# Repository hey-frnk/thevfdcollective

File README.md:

# Fluorescence by The VFD Collective

Glad to see you, welcome to the repository of Fluorescence by The VFD Collective. While having a colorful time, here are a few places to roam freely:
  - FluorescenceV3: (active) Source code of firmware version 3.0 for OpenVFD & Fluorescence. Includes source code for Arduino, STM32 HAL and simulation with Qt GUI
  - FluorescenceApp: (active) Source code of the app for OpenVFD & Fluorescence. The cross platform app enables communicating to Fluorescence over USB and Bluetooth
  
  - FluorescenceCompiled: (active) Official compiled versions of FluorescenceApp and firmware files for Fluorescence
  - hardware: (active) Public Fluorescence/OpenVFD Eagle files. Includes libraries and published PCB designs

No longer updated, kept for reference only:
  - openvfd_firmware: (V2 Legacy) Those sparking code lines for OpenVFD & Fluorescence. The cool thing about the firmware is that it is only one single file. Throw it into your Arduino IDE, compile and have fun. Oh and don't forget to tear it apart and get creative yourself
  - myOpenVFD-vs: (V2 Legacy) Source code of myOpenVFD Windows application

Cheers.</br>
Frank from The VFD Collective

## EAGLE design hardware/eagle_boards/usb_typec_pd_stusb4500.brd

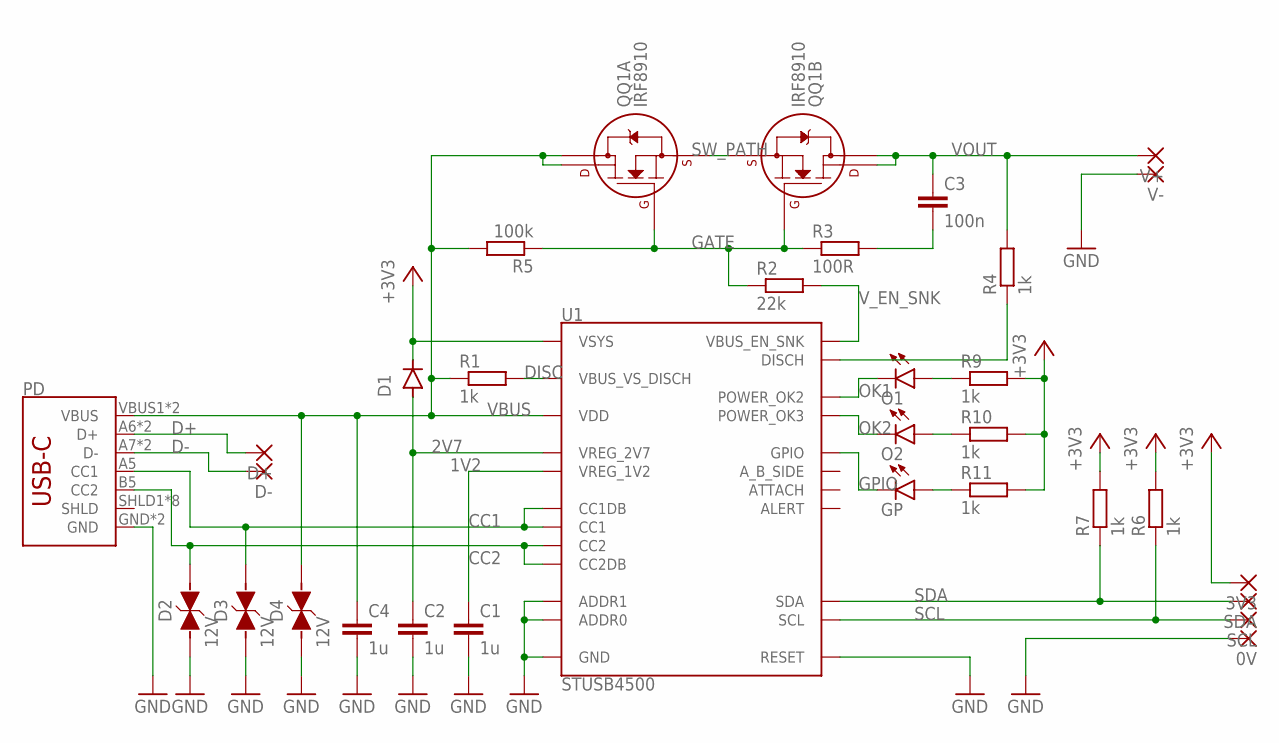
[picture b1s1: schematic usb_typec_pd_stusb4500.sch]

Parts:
0V, 3V3: SMD2; SMD1,27-2,54
C1, C2, C4: 1u; C0805
C3: 100n; C0805
D1: DIODE-SOD123; SOD123
D2, D3, D4: 12V; WE-VE_0805
D+: SMD2; SMD1,27-2,54
D-: SMD2; SMD1,27-2,54
GP: LEDCHIP-LED0805; CHIP-LED0805
O1, O2: LEDCHIP-LED0805; CHIP-LED0805
PD: USB-TYPEC-16PIN2-LAYER; USB-C-16P
QQ1: IRF8910; SO-8
R1, R4, R6, R7, R9, R10, R11: 1k; R0805
R2: 22k; R0805
R3: 100R; R0805
R5: 100k; R0805
SCL: SMD2; SMD1,27-2,54
SDA: SMD2; SMD1,27-2,54
U1: STUSB4500; POWER-QFN-24
V+: SMD2; SMD1,27-2,54
V-: SMD2; SMD1,27-2,54

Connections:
1V2: C1.1, U1.P$21 (VREG_1V2)
2V7: C2.1, D1.A, U1.P$23 (VREG_2V7)
+3V3: 3V3.1, D1.C, R6.2, R7.2, R9.2, R10.2, R11.2, U1.P$22 (VSYS)
CC1: D3.1, PD.A5 (CC1), U1.P$1 (CC1DB), U1.P$2 (CC1)
CC2: D2.1, PD.B5 (CC2), U1.P$4 (CC2), U1.P$5 (CC2DB)
D+: D+.1, PD.A6 (D+), PD.B6 (D+)
D-: D-.1, PD.A7 (D-), PD.B7 (D-)
DISC: R1.2, U1.P$18 (VBUS_VS_DISCH)
GATE: QQ1.2 (G), QQ1.4 (G), R2.1, R3.1, R5.1
GND: 0V.1, C1.2, C2.2, C4.2, D2.2, D3.2, D4.2, PD.GND, PD.GND2 (GND), U1.P$6 (RESET), U1.P$10 (GND), U1.P$12 (ADDR0), U1.P$13 (ADDR1), U1.P$25 (GND), V-.1
GPIO: GP.C, U1.P$15 (GPIO)
unnamed: C3.2, R3.2
unnamed: R4.1, U1.P$9 (DISCH)
unnamed: O1.A, R9.1
unnamed: O2.A, R10.1
unnamed: GP.A, R11.1
OK1: O1.C, U1.P$20 (POWER_OK2)
OK2: O2.C, U1.P$14 (POWER_OK3)
SCL: R6.1, SCL.1, U1.P$7 (SCL)
SDA: R7.1, SDA.1, U1.P$8 (SDA)
SW_PATH: QQ1.1 (S), QQ1.3 (S)
VBUS: C4.1, D4.1, PD.VBUS1 (VBUS), PD.VBUS2 (VBUS), QQ1.7 (D2), QQ1.8 (D1), R1.1, R5.2, U1.P$24 (VDD)
VOUT: C3.1, QQ1.5 (D2), QQ1.6 (D1), R4.2, V+.1
V_EN_SNK: R2.2, U1.P$16 (VBUS_EN_SNK)

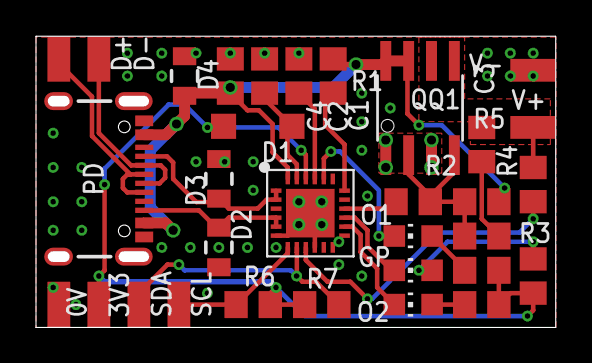
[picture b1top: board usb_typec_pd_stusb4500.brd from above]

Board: 2 copper layers, 28.9 x 16.2 mm, 32 parts (0 on the bottom side), 24 nets.

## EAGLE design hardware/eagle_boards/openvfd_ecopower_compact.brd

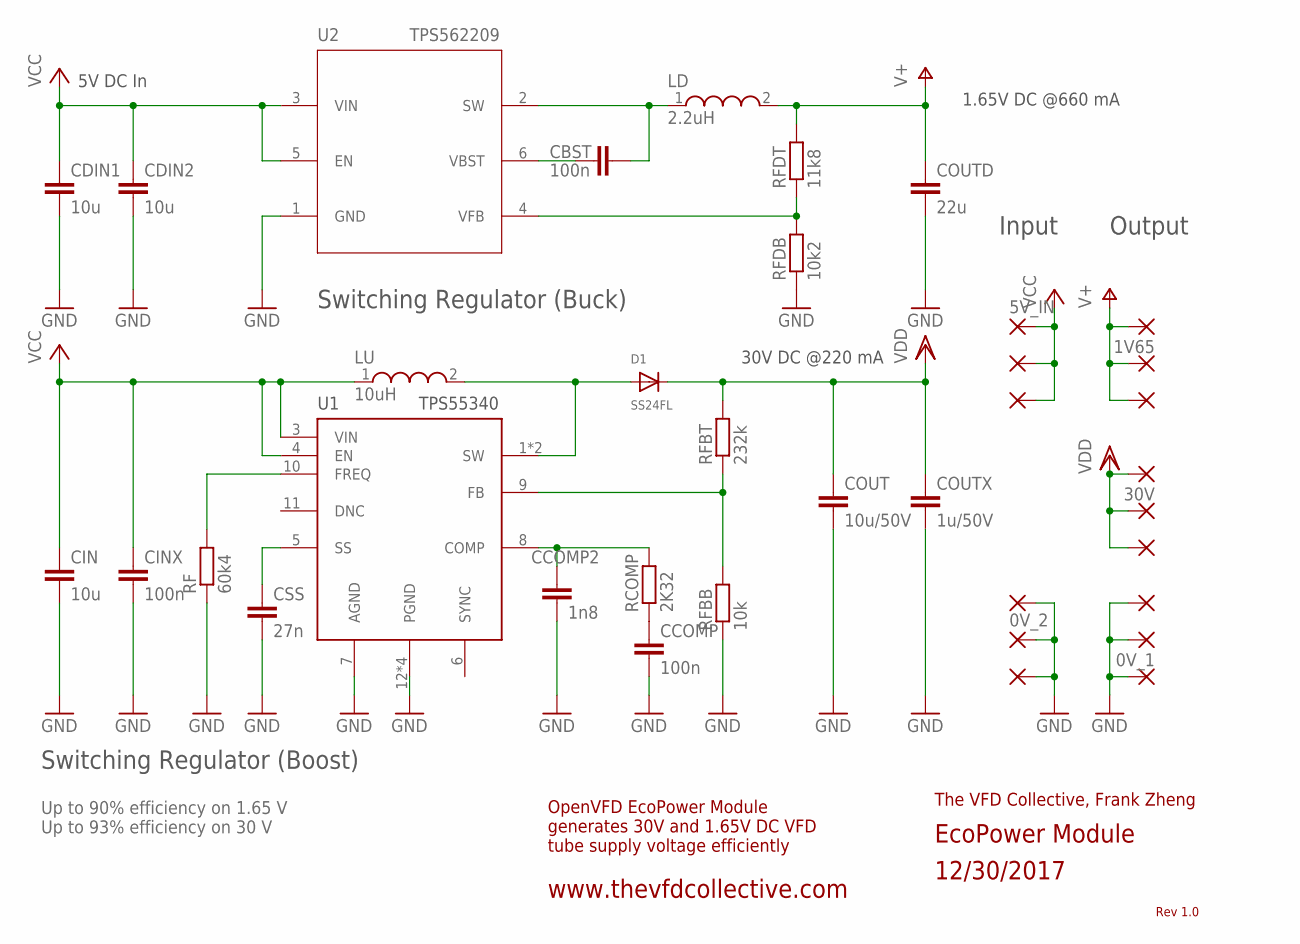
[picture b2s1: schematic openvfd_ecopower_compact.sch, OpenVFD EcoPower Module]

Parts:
0V_1, 0V_2, 0V_3, 0V_4, 1V1, 1V65, 5V_IN, 5V_IN1, 30V, 30V1: SMD2; SMD1,27-2,54
CBST: 100n; C0805
CCOMP: 100n; C0805
CCOMP2: 1n8; C0805
CDIN1, CDIN2: 10u; C0805
CIN: 10u; C0805
CINX: 100n; C0805
COUT: 10u/50V; C1206
COUTD: 22u; C0805
COUTX: 1u/50V; C0805
CSS: 27n; C0805
D1: SS24FL; SOD-123FL
LD: 2.2uH; WE-TPC_4818/4828
LU: 10uH; WE-LQS_6045
PAD1, PAD2, PAD3, PAD4, PAD5: 1,6/0,8
RCOMP: 2K32; R0805
RF: 60k4; R0805
RFBB: 10k; R0805
RFBT: 232k; R0805
RFDB: 10k2; R0805
RFDT: 11k8; R0805
U1: TPS55340; HTSSOP-14
U2: TPS562209; SOT-23(6)

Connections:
COMP: CCOMP2.1, RCOMP.2, U1.8 (COMP)
FB: RFBB.2, RFBT.1, U1.9 (FB)
FREQ: RF.2, U1.10 (FREQ)
GND: 0V_1.1, 0V_2.1, 0V_3.1, 0V_4.1, CCOMP.2, CCOMP2.2, CDIN1.2, CDIN2.2, CIN.2, CINX.2, COUT.2, COUTD.2, COUTX.2, CSS.2, PAD1.1, PAD5.1, RF.1, RFBB.1, RFDB.1, U1.7 (AGND), U1.12 (PGND), U1.13 (PGND), U1.14 (PGND), U1.15 (PGND), U2.1 (GND)
unnamed: CCOMP.1, RCOMP.1
unnamed: CBST.1, U2.6 (VBST)
unnamed: RFDB.2, RFDT.1, U2.4 (VFB)
SS: CSS.1, U1.5 (SS)
SW: D1.A, LU.2, U1.1 (SW), U1.2 (SW)
V+: 1V1.1, 1V65.1, COUTD.1, LD.2, PAD3.1, RFDT.2
VCC: 5V_IN.1, 5V_IN1.1, CDIN1.1, CDIN2.1, CIN.1, CINX.1, LU.1, PAD2.1, U1.3 (VIN), U1.4 (EN), U2.3 (VIN), U2.5 (EN)
VDD: 30V.1, 30V1.1, COUT.1, COUTX.1, D1.C, PAD4.1, RFBT.2
VSW_D: CBST.2, LD.1, U2.2 (SW)

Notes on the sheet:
Input
Output
30V DC @220 mA
1.65V DC @660 mA
EcoPower Module
12/30/2017
5V DC In
Up to 90% efficiency on 1.65 V Up to 93% efficiency on 30 V
Rev 1.0
OpenVFD EcoPower Module generates 30V and 1.65V DC VFD tube supply voltage efficiently
www.thevfdcollective.com
The VFD Collective, Frank Zheng
Switching Regulator (Buck)
Switching Regulator (Boost)

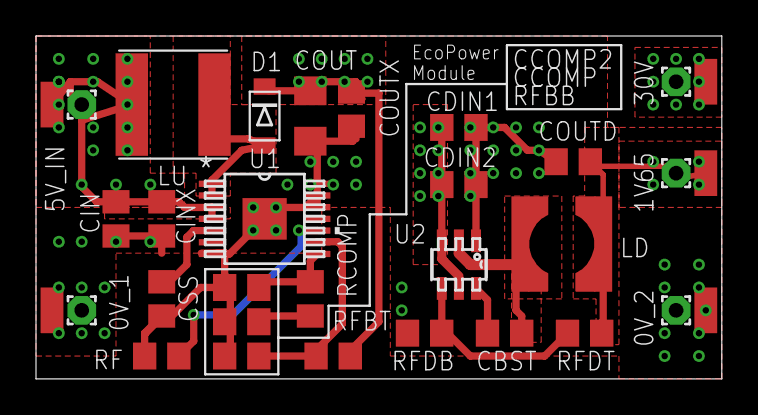
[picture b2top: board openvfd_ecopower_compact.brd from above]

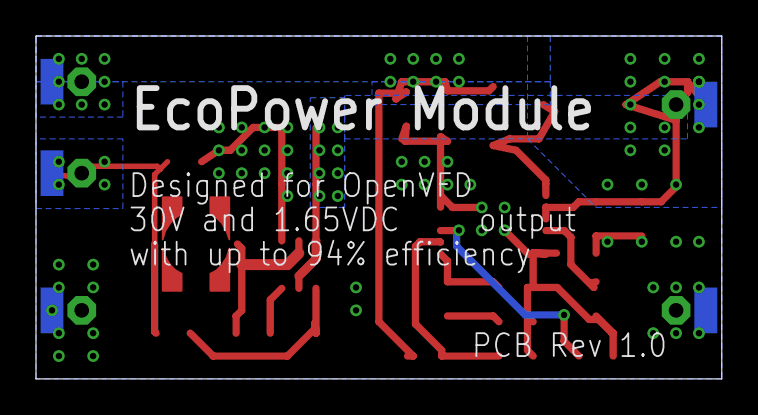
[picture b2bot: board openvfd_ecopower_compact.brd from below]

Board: 2 copper layers, 38.1 x 19.1 mm, 37 parts (5 on the bottom side), 13 nets.

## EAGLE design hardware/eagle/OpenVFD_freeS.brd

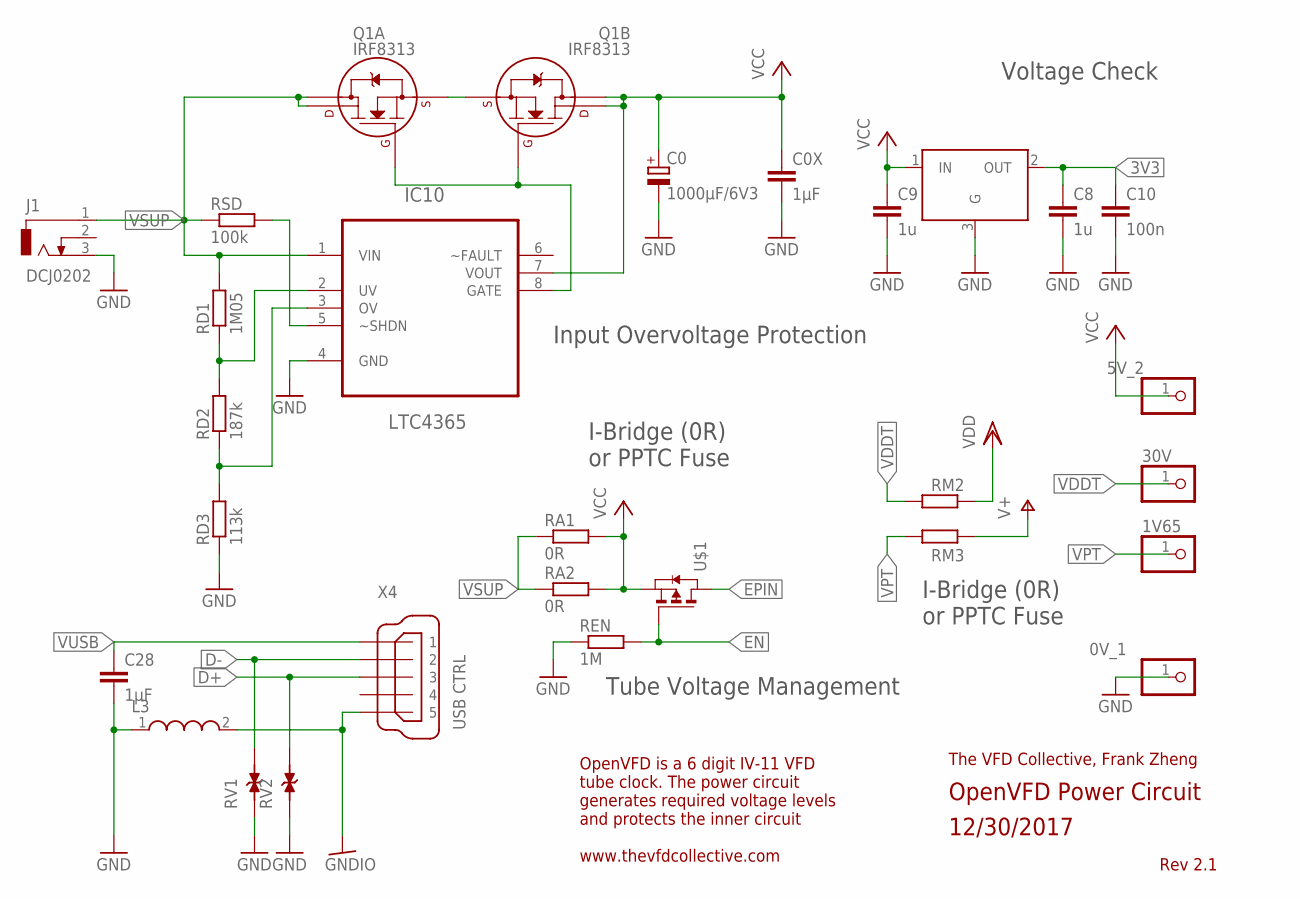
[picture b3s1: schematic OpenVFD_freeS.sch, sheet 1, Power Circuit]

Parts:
0V_1, 1V65, 5V_2, 30V: PINHD-1X1; 1X01
C0: 1000µF/6V3; 153CLV-1010
C0X, C28: 1µF; C0805
C8, C9: 1u; C0805
C10: 100n; C0805
IC9: AP7313; SOT23-R
IC10: LTC4365; SOT65P280X100-8N
J1: DCJ0202
L3: WE-CBF_0805(HC); WE-CBF_0805(W=4.0)
Q1: IRF8313; SO-8
RA1, RA2: 0R; R1210
RD1: 1M05; R0805
RD2: 187k; R0805
RD3: 113k; R0805
REN: 1M; R0805
RM2, RM3: 0R; R1210
RSD: 100k; R0805
RV1, RV2: WE-VE_0805_82350120101; WESURGE_0805_REFLOW
U$1: PMOSSOT223; SOT223
X4: USB CTRL; 32005-201

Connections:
3V3: C8.1, C10.1, IC9.2 (OUT); also elsewhere on the board
D+: RV2.1, X4.3; also elsewhere on the board
D-: RV1.1, X4.2; also elsewhere on the board
GATE: IC10.8 (GATE), Q1.2 (G), Q1.4 (G)
GNDIO: L3.2, X4.5; also elsewhere on the board
unnamed: REN.2, U$1.1 (G)
OV: IC10.3 (OV), RD2.1, RD3.2
SHDN: IC10.5 (~SHDN), RSD.2
SOURCE: Q1.1 (S), Q1.3 (S)
UV: IC10.2 (UV), RD1.1, RD2.2
V+: RM3.2; also elsewhere on the board
VDD: RM2.2; also elsewhere on the board
VDDT: 30V.1, RM2.1; also elsewhere on the board
VPT: 1V65.1, RM3.1; also elsewhere on the board
VSUP: IC10.1 (VIN), J1.1, Q1.7 (D2), Q1.8 (D1), RA1.1, RA2.1, RD1.2, RSD.1

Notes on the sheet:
Input Overvoltage Protection
I-Bridge (0R) or PPTC Fuse
Tube Voltage Management
Voltage Check
The VFD Collective, Frank Zheng
OpenVFD Power Circuit
12/30/2017
Rev 2.1
OpenVFD is a 6 digit IV-11 VFD tube clock. The power circuit generates required voltage levels and protects the inner circuit www.thevfdcollective.com

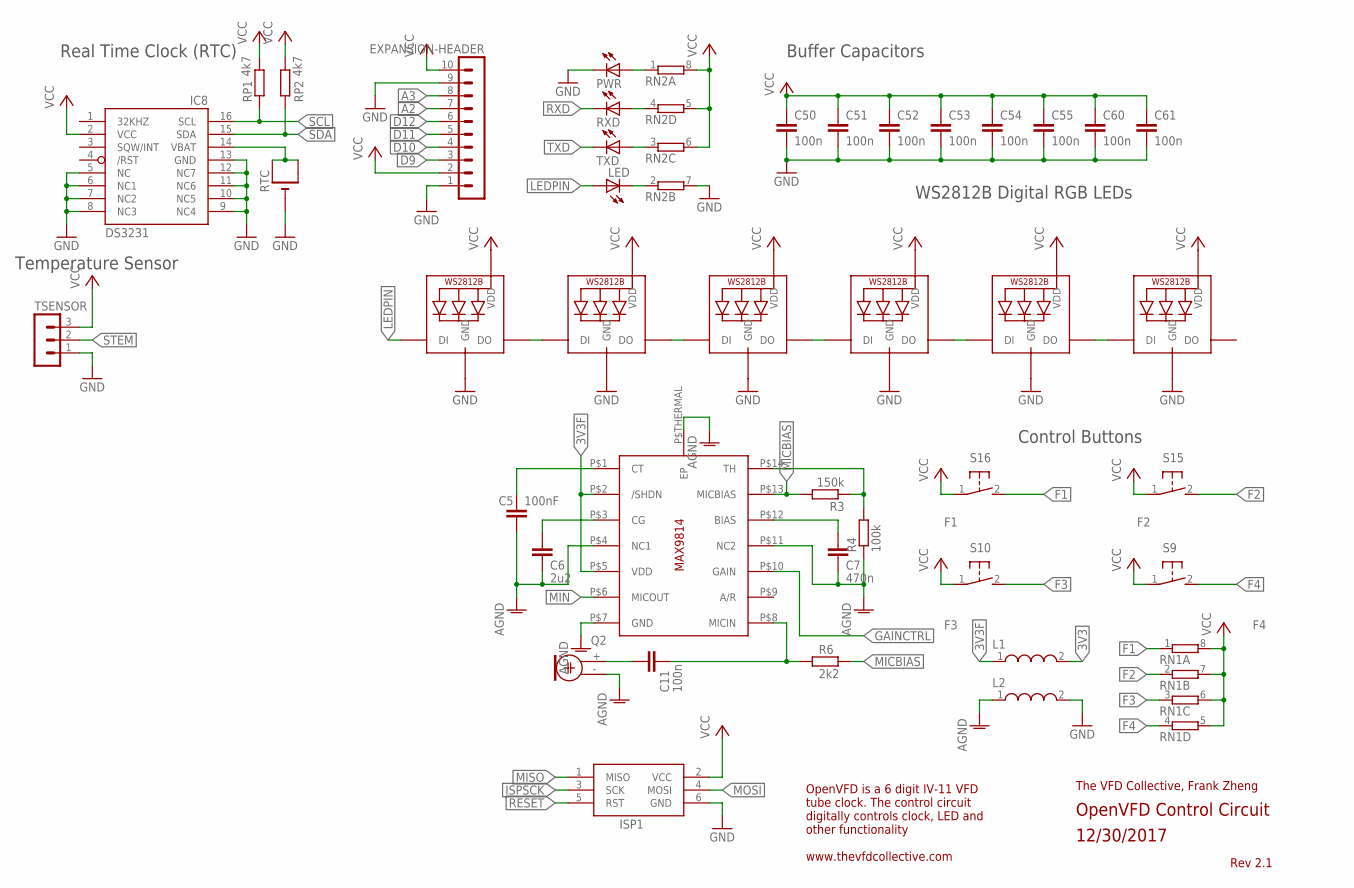
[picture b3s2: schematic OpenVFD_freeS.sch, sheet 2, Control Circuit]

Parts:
C5: 100nF; C0805
C6: 2u2; C0805
C7: 470n; C0805
C11, C50, C51, C52, C53, C54, C55, C60, C61: 100n; C0805
EXPANSION-HEADER: MA10-1
IC7: MAX9814TDFN14; TDFN14_3X3MM
IC8: DS3231; SO16W
ISP1: AVRISP-6; AVRISP
L1, L2: WE-CBF_0805(HC); WE-CBF_0805(W=4.0)
LED: LEDCHIP-LED0805; CHIP-LED0805
LED1, LED2, LED3, LED4, LED5, LED6: WS2812B5050; WS2812B
PWR: LEDCHIP-LED0805; CHIP-LED0805
Q2: ELECTRET; 9.7ELECTRET
R3: 150k; R0805
R4: 100k; R0805
R6: 2k2; R0805
RN1, RN2: 4R-N0603-ARV; 0603-ARV
RP1, RP2: 4k7; R0805
RTC: CR1220SMT; CR1220-SMD
RXD: LEDCHIP-LED0805; CHIP-LED0805
S9: F4; B3F-31XX
S10: F3; B3F-31XX
S15: F2; B3F-31XX
S16: F1; B3F-31XX
TSENSOR: MA03-1
TXD: LEDCHIP-LED0805; CHIP-LED0805

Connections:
3V3: L1.2; also elsewhere on the board
3V3F: IC7.P$2 (/SHDN), IC7.P$5 (VDD), L1.1
A2: EXPANSION-HEADER.7; also elsewhere on the board
A3: EXPANSION-HEADER.8; also elsewhere on the board
AGND: C5.2, C6.2, C7.2, IC7.P$4 (NC1), IC7.P$7 (GND), IC7.P$11 (NC2), IC7.P$THERMAL (EP), L2.1, Q2.- (1), R4.1
D9: EXPANSION-HEADER.3; also elsewhere on the board
D10: EXPANSION-HEADER.4; also elsewhere on the board
D11: EXPANSION-HEADER.5; also elsewhere on the board
D12: EXPANSION-HEADER.6; also elsewhere on the board
F1: RN1.1, S16.2 (S); also elsewhere on the board
F2: RN1.2 (1), S15.2 (S); also elsewhere on the board
F3: RN1.3 (1), S10.2 (S); also elsewhere on the board
F4: RN1.4 (1), S9.2 (S); also elsewhere on the board
GAINCTRL: IC7.P$10 (GAIN)
ISPSCK: ISP1.3 (SCK); also elsewhere on the board
LD1: LED1.2-DOUT (DO), LED2.4-DIN (DI)
LD2: LED2.2-DOUT (DO), LED3.4-DIN (DI)
LD3: LED3.2-DOUT (DO), LED4.4-DIN (DI)
LD4: LED4.2-DOUT (DO), LED5.4-DIN (DI)
LD5: LED5.2-DOUT (DO), LED6.4-DIN (DI)
LEDPIN: LED.A, LED1.4-DIN (DI); also elsewhere on the board
MIC+: C11.1, Q2.+ (2)
MICBIAS: IC7.P$13 (MICBIAS), R3.2, R6.2
MIN: IC7.P$6 (MICOUT); also elsewhere on the board
MISO: ISP1.1 (MISO); also elsewhere on the board
MOSI: ISP1.4 (MOSI); also elsewhere on the board
unnamed: RN2.4 (1), RXD.A
unnamed: RN2.3 (1), TXD.A
unnamed: LED.C, RN2.2 (1)
unnamed: PWR.A, RN2.1
unnamed: C5.1, IC7.P$1 (CT)
unnamed: C6.1, IC7.P$3 (CG)
unnamed: IC7.P$14 (TH), R3.1, R4.2
unnamed: C7.1, IC7.P$12 (BIAS)
unnamed: C11.2, IC7.P$8 (MICIN), R6.1
RESET: ISP1.5 (RST); also elsewhere on the board
RXD: RXD.C; also elsewhere on the board
SCL: IC8.16 (SCL), RP1.1; also elsewhere on the board
SDA: IC8.15 (SDA), RP2.1; also elsewhere on the board
STEM: TSENSOR.2; also elsewhere on the board
TXD: TXD.C; also elsewhere on the board
VBAT: IC8.14 (VBAT), RTC.+$1 (+), RTC.+$2 (+1)

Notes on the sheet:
The VFD Collective, Frank Zheng
OpenVFD Control Circuit
12/30/2017
Rev 2.1
OpenVFD is a 6 digit IV-11 VFD tube clock. The control circuit digitally controls clock, LED and other functionality www.thevfdcollective.com
Real Time Clock (RTC)
Buffer Capacitors
Temperature Sensor
WS2812B Digital RGB LEDs
Control Buttons

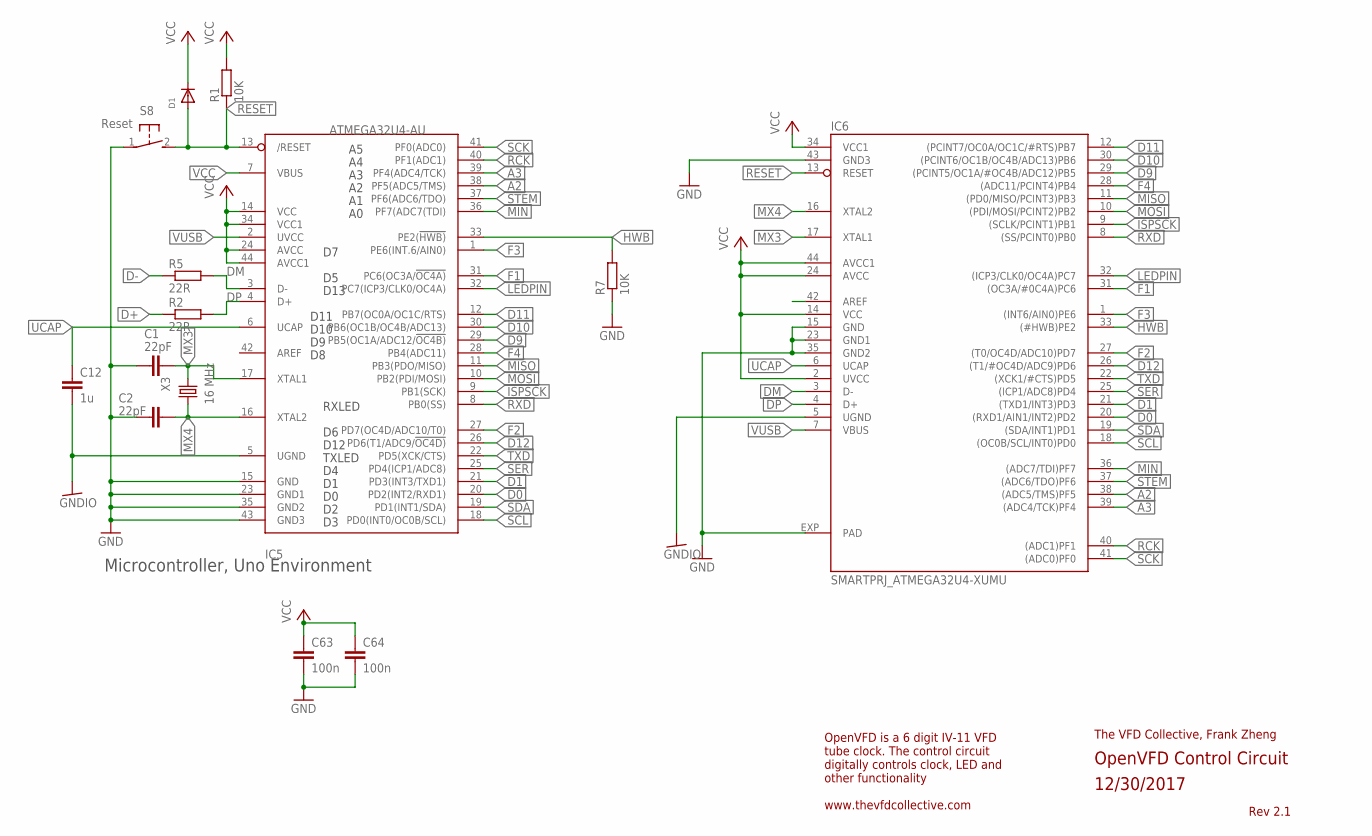
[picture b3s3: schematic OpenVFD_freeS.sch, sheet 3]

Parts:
C1, C2: 22pF; C0805
C12: 1u; C0805
C63, C64: 100n; C0805
D1: DIODE_SOD-123FL; SOD-123FL
IC5: ATMEGA32U4-AU; TQFP44
IC6: SMARTPRJ_ATMEGA32U4-XUMU; SMARTPRJ_QFN44ML7X7
R1, R7: 10K; R0805
R2, R5: 22R; R0805
S8: Reset; B3F-31XX
X3: 16 MHz; CTS406

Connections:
A2: IC5.38 (PF5(ADC5/TMS)), IC6.38 ((ADC5/TMS)PF5); also elsewhere on the board
A3: IC5.39 (PF4(ADC4/TCK)), IC6.39 ((ADC4/TCK)PF4); also elsewhere on the board
D9: IC5.29 (PB5(OC1A/ADC12/!OC4B)), IC6.29 ((PCINT5/OC1A/#OC4B/ADC12)PB5); also elsewhere on the board
D10: IC5.30 (PB6(OC1B/OC4B/ADC13)), IC6.30 ((PCINT6/OC1B/OC4B/ADC13)PB6); also elsewhere on the board
D11: IC5.12 (PB7(OC0A/OC1C/RTS)), IC6.12 ((PCINT7/OC0A/OC1C/#RTS)PB7); also elsewhere on the board
D12: IC5.26 (PD6(T1/ADC9/!OC4D)), IC6.26 ((T1/#OC4D/ADC9)PD6); also elsewhere on the board
D+: R2.1; also elsewhere on the board
D-: R5.1; also elsewhere on the board
DM: IC5.3 (D-), IC6.3 (D-), R5.2
DP: IC5.4 (D+), IC6.4 (D+), R2.2
F1: IC5.31 (PC6(OC3A/!OC4A)), IC6.31 ((OC3A/#0C4A)PC6); also elsewhere on the board
F2: IC5.27 (PD7(OC4D/ADC10/T0)), IC6.27 ((T0/OC4D/ADC10)PD7); also elsewhere on the board
F3: IC5.1 (PE6(INT.6/AIN0)), IC6.1 ((INT6/AIN0)PE6); also elsewhere on the board
F4: IC5.28 (PB4(ADC11)), IC6.28 ((ADC11/PCINT4)PB4); also elsewhere on the board
GNDIO: C12.2, IC5.5 (UGND), IC6.5 (UGND); also elsewhere on the board
HWB: IC5.33 (PE2(!HWB)), IC6.33 ((#HWB)PE2), R7.2
IRQ: IC5.20 (PD2(INT2/RXD1)), IC6.20 ((RXD1/AIN1/INT2)PD2); also elsewhere on the board
ISPSCK: IC5.9 (PB1(SCK)), IC6.9 ((SCLK/PCINT1)PB1); also elsewhere on the board
LEDPIN: IC5.32 (PC7(ICP3/CLK0/OC4A)), IC6.32 ((ICP3/CLK0/OC4A)PC7); also elsewhere on the board
MIN: IC5.36 (PF7(ADC7(TDI)), IC6.36 ((ADC7/TDI)PF7); also elsewhere on the board
MISO: IC5.11 (PB3(PDO/MISO)), IC6.11 ((PD0/MISO/PCINT3)PB3); also elsewhere on the board
MOSI: IC5.10 (PB2(PDI/MOSI)), IC6.10 ((PDI/MOSI/PCINT2)PB2); also elsewhere on the board
MX3: C1.2, IC5.17 (XTAL1), IC6.17 (XTAL1), X3.3 (2)
MX4: C2.2, IC5.16 (XTAL2), IC6.16 (XTAL2), X3.1
RCK: IC5.40 (PF1(ADC1)), IC6.40 ((ADC1)PF1); also elsewhere on the board
RESET: D1.A, IC5.13 (/RESET), IC6.13 (RESET), R1.1, S8.2 (S); also elsewhere on the board
RXD: IC5.8 (PB0(SS)), IC6.8 ((SS/PCINT0)PB0); also elsewhere on the board
SCK: IC5.41 (PF0(ADC0)), IC6.41 ((ADC0)PF0); also elsewhere on the board
SCL: IC5.18 (PD0(INT0/OC0B/SCL)), IC6.18 ((OC0B/SCL/INT0)PD0); also elsewhere on the board
SDA: IC5.19 (PD1(INT1/SDA)), IC6.19 ((SDA/INT1)PD1); also elsewhere on the board
SER: IC5.25 (PD4(ICP1/ADC8)), IC6.25 ((ICP1/ADC8)PD4); also elsewhere on the board
STEM: IC5.37 (PF6(ADC6/TDO)), IC6.37 ((ADC6/TDO)PF6); also elsewhere on the board
TXD: IC5.22 (PD5(XCK/CTS)), IC6.22 ((XCK1/#CTS)PD5); also elsewhere on the board
UCAP: C12.1, IC5.6 (UCAP), IC6.6 (UCAP)

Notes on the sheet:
Microcontroller, Uno Environment
D11
D10
D12
D13
RXLED
TXLED
The VFD Collective, Frank Zheng
OpenVFD Control Circuit
12/30/2017
Rev 2.1
OpenVFD is a 6 digit IV-11 VFD tube clock. The control circuit digitally controls clock, LED and other functionality www.thevfdcollective.com

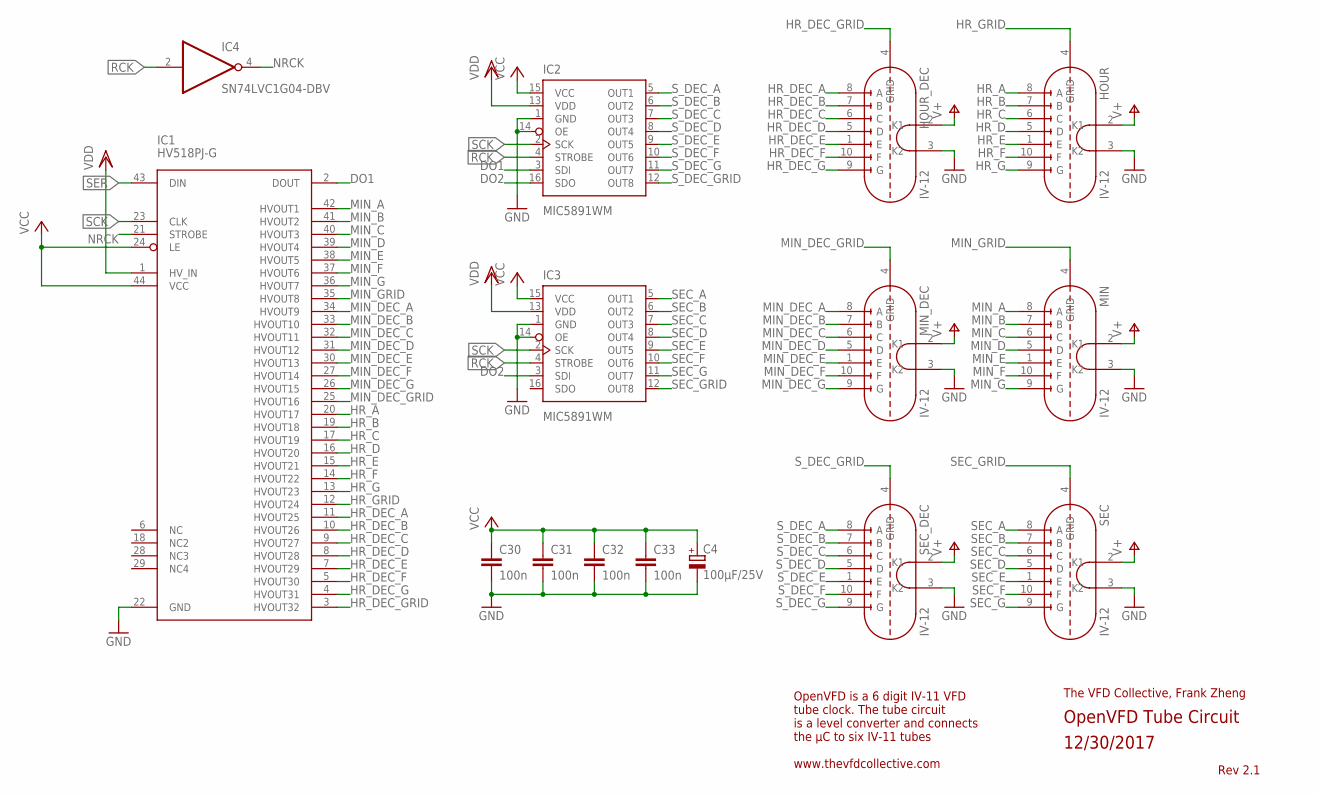
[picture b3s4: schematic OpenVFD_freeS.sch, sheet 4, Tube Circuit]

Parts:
C4: 100µF/25V; 153CLV-0605
C30, C31, C32, C33: 100n; C0805
HOUR: IV-12
HOUR_DEC: IV-12
IC1: HV518PJ-G; PLCC44S
IC2, IC3: MIC5891WM; SO-16DW
IC4: SN74LVC1G04-DBV; SOT23-5
MIN: IV-12
MIN_DEC: IV-12
SEC: IV-12
SEC_DEC: IV-12

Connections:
DO1: IC1.2 (DOUT), IC2.3 (SDI)
DO2: IC2.16 (SDO), IC3.3 (SDI)
HR_A: HOUR.8 (A), IC1.20 (HVOUT17)
HR_B: HOUR.7 (B), IC1.19 (HVOUT18)
HR_C: HOUR.6 (C), IC1.17 (HVOUT19)
HR_D: HOUR.5 (D), IC1.16 (HVOUT20)
HR_DEC_A: HOUR_DEC.8 (A), IC1.11 (HVOUT25)
HR_DEC_B: HOUR_DEC.7 (B), IC1.10 (HVOUT26)
HR_DEC_C: HOUR_DEC.6 (C), IC1.9 (HVOUT27)
HR_DEC_D: HOUR_DEC.5 (D), IC1.8 (HVOUT28)
HR_DEC_E: HOUR_DEC.1 (E), IC1.7 (HVOUT29)
HR_DEC_F: HOUR_DEC.10 (F), IC1.5 (HVOUT30)
HR_DEC_G: HOUR_DEC.9 (G), IC1.4 (HVOUT31)
HR_DEC_GRID: HOUR_DEC.4 (GRID), IC1.3 (HVOUT32)
HR_E: HOUR.1 (E), IC1.15 (HVOUT21)
HR_F: HOUR.10 (F), IC1.14 (HVOUT22)
HR_G: HOUR.9 (G), IC1.13 (HVOUT23)
HR_GRID: HOUR.4 (GRID), IC1.12 (HVOUT24)
MIN_A: IC1.42 (HVOUT1), MIN.8 (A)
MIN_B: IC1.41 (HVOUT2), MIN.7 (B)
MIN_C: IC1.40 (HVOUT3), MIN.6 (C)
MIN_D: IC1.39 (HVOUT4), MIN.5 (D)
MIN_DEC_A: IC1.34 (HVOUT9), MIN_DEC.8 (A)
MIN_DEC_B: IC1.33 (HVOUT10), MIN_DEC.7 (B)
MIN_DEC_C: IC1.32 (HVOUT11), MIN_DEC.6 (C)
MIN_DEC_D: IC1.31 (HVOUT12), MIN_DEC.5 (D)
MIN_DEC_E: IC1.30 (HVOUT13), MIN_DEC.1 (E)
MIN_DEC_F: IC1.27 (HVOUT14), MIN_DEC.10 (F)
MIN_DEC_G: IC1.26 (HVOUT15), MIN_DEC.9 (G)
MIN_DEC_GRID: IC1.25 (HVOUT16), MIN_DEC.4 (GRID)
MIN_E: IC1.38 (HVOUT5), MIN.1 (E)
MIN_F: IC1.37 (HVOUT6), MIN.10 (F)
MIN_G: IC1.36 (HVOUT7), MIN.9 (G)
MIN_GRID: IC1.35 (HVOUT8), MIN.4 (GRID)
NRCK: IC1.21 (STROBE), IC4.4 (Y)
RCK: IC2.4 (STROBE), IC3.4 (STROBE), IC4.2 (A); also elsewhere on the board
SCK: IC1.23 (CLK), IC2.2 (SCK), IC3.2 (SCK); also elsewhere on the board
SEC_A: IC3.5 (OUT1), SEC.8 (A)
SEC_B: IC3.6 (OUT2), SEC.7 (B)
SEC_C: IC3.7 (OUT3), SEC.6 (C)
SEC_D: IC3.8 (OUT4), SEC.5 (D)
SEC_E: IC3.9 (OUT5), SEC.1 (E)
SEC_F: IC3.10 (OUT6), SEC.10 (F)
SEC_G: IC3.11 (OUT7), SEC.9 (G)
SEC_GRID: IC3.12 (OUT8), SEC.4 (GRID)
SER: IC1.43 (DIN); also elsewhere on the board
S_DEC_A: IC2.5 (OUT1), SEC_DEC.8 (A)
S_DEC_B: IC2.6 (OUT2), SEC_DEC.7 (B)
S_DEC_C: IC2.7 (OUT3), SEC_DEC.6 (C)
S_DEC_D: IC2.8 (OUT4), SEC_DEC.5 (D)
S_DEC_E: IC2.9 (OUT5), SEC_DEC.1 (E)
S_DEC_F: IC2.10 (OUT6), SEC_DEC.10 (F)
S_DEC_G: IC2.11 (OUT7), SEC_DEC.9 (G)
S_DEC_GRID: IC2.12 (OUT8), SEC_DEC.4 (GRID)
V+: HOUR.2 (K1), HOUR_DEC.2 (K1), MIN.2 (K1), MIN_DEC.2 (K1), SEC.2 (K1), SEC_DEC.2 (K1); also elsewhere on the board
VDD: IC1.1 (HV_IN), IC2.13 (VDD), IC3.13 (VDD); also elsewhere on the board

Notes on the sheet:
The VFD Collective, Frank Zheng
OpenVFD Tube Circuit
12/30/2017
Rev 2.1
OpenVFD is a 6 digit IV-11 VFD tube clock. The tube circuit is a level converter and connects the µC to six IV-11 tubes www.thevfdcollective.com

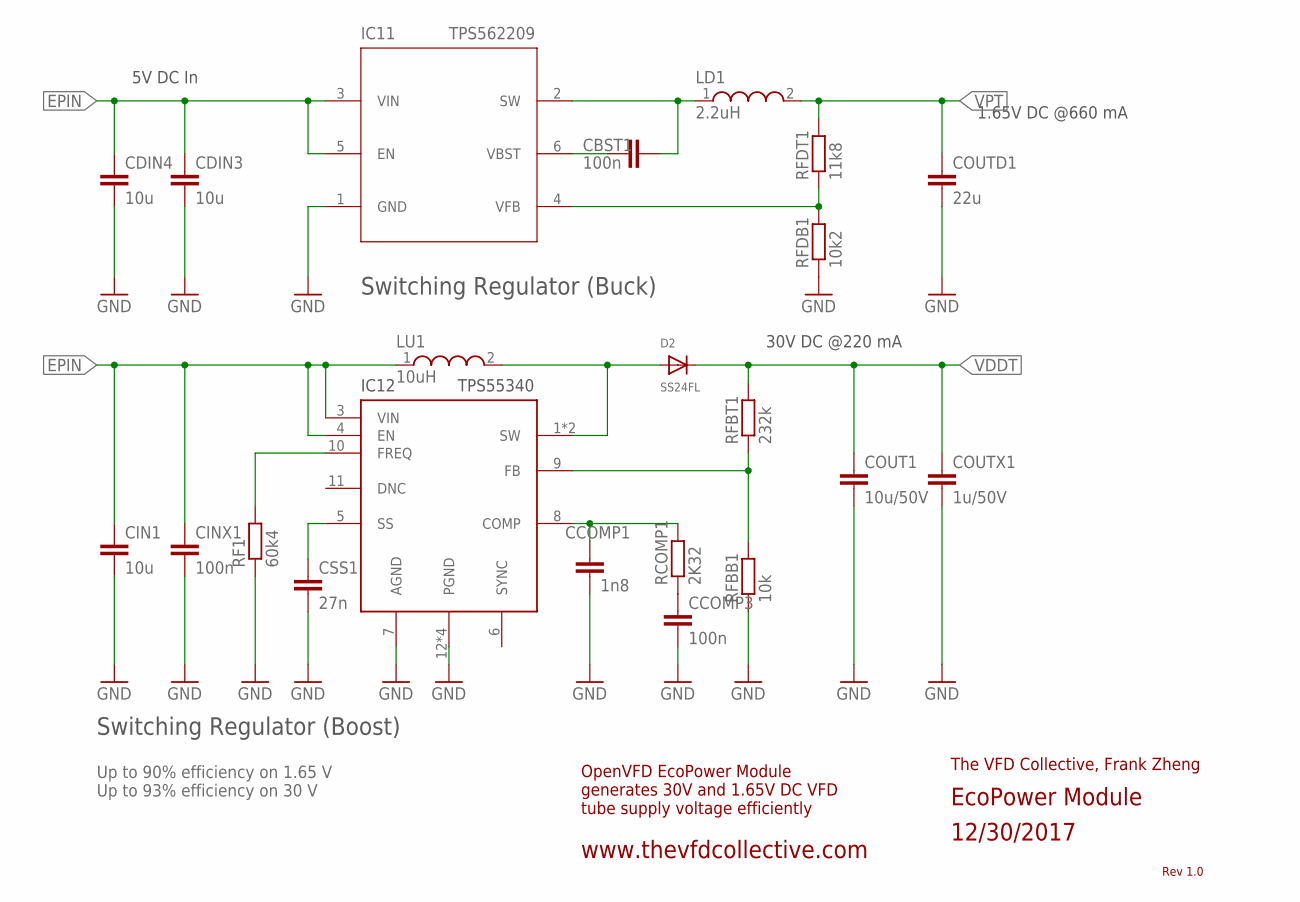
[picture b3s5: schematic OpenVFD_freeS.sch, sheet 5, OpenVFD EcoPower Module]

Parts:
CBST1: 100n; C0805
CCOMP1: 1n8; C0805
CCOMP3: 100n; C0805
CDIN3, CDIN4: 10u; C0805
CIN1: 10u; C0805
CINX1: 100n; C0805
COUT1: 10u/50V; C1206
COUTD1: 22u; C0805
COUTX1: 1u/50V; C0805
CSS1: 27n; C0805
D2: SS24FL; SOD-123FL
IC11: TPS562209; SOT-23(6)
IC12: TPS55340; HTSSOP-14
LD1: 2.2uH; WE-TPC_4818/4828
LU1: 10uH; WE-LQS_6045
RCOMP1: 2K32; R0805
RF1: 60k4; R0805
RFBB1: 10k; R0805
RFBT1: 232k; R0805
RFDB1: 10k2; R0805
RFDT1: 11k8; R0805

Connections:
COMP1: CCOMP1.1, IC12.8 (COMP), RCOMP1.2
FB1: IC12.9 (FB), RFBB1.2, RFBT1.1
FREQ1: IC12.10 (FREQ), RF1.2
unnamed: CCOMP3.1, RCOMP1.1
unnamed: CBST1.1, IC11.6 (VBST)
unnamed: IC11.4 (VFB), RFDB1.2, RFDT1.1
SS1: CSS1.1, IC12.5 (SS)
SW1: D2.A, IC12.1 (SW), IC12.2 (SW), LU1.2
VDDT: COUT1.1, COUTX1.1, D2.C, RFBT1.2; also elsewhere on the board
VPT: COUTD1.1, LD1.2, RFDT1.2; also elsewhere on the board
VSW_D1: CBST1.2, IC11.2 (SW), LD1.1

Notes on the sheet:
30V DC @220 mA
1.65V DC @660 mA
EcoPower Module
12/30/2017
5V DC In
Up to 90% efficiency on 1.65 V Up to 93% efficiency on 30 V
Rev 1.0
OpenVFD EcoPower Module generates 30V and 1.65V DC VFD tube supply voltage efficiently
www.thevfdcollective.com
The VFD Collective, Frank Zheng
Switching Regulator (Buck)
Switching Regulator (Boost)

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
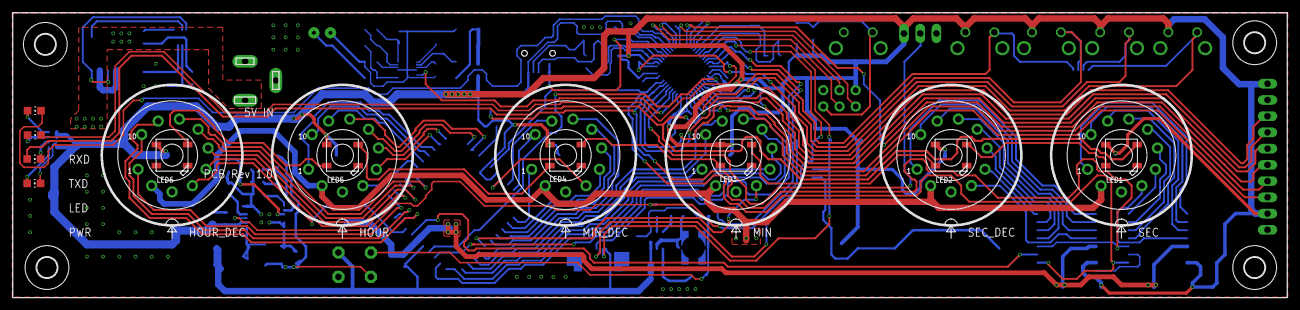
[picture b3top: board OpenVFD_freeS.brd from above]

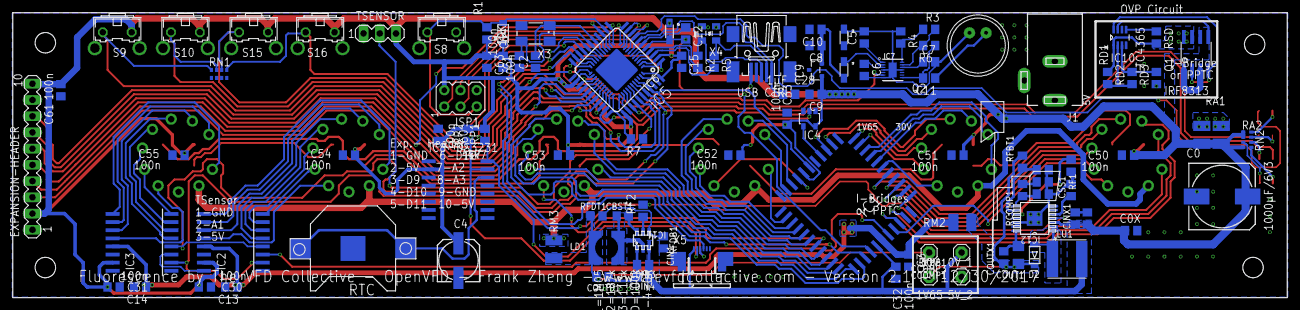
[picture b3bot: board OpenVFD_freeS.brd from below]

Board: 2 copper layers, 199.5 x 44.6 mm, 129 parts (109 on the bottom side), 129 nets.

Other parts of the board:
C3, C13, C14, C15: 100n; C0805
RF2: 60k4; R0805
U$2, U$3, U$4, U$5: 3,2
X5: 52745-0690

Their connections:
IRQ: X5.4; also elsewhere on the board
SCL: X5.3; also elsewhere on the board
SDA: X5.2; also elsewhere on the board
VDD: C3.1, C13.1, C14.1; also elsewhere on the board

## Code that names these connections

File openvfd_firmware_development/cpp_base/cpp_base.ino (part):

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#include "LED_Color_Serial.hpp"
#include "LED_Mode_Manager.hpp"

// Remove comment to enable temperature sensor reading at STEM pin (DS18B20)
// #define    TEMPERATURE_ENABLE

#ifdef TEMPERATURE_ENABLE
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//         Pin Name  | A | ATMEGA Mapping | Comment, Schematics Signal Name
// ------------------------------------------------------------------------------------------
#define    CLOCK_PIN   2    // ATMEGA:  4   74HC595 SPI Clock Pin, SCK
#define    LATCH_PIN   3    // ATMEGA:  5   74HC595 SPI Latch Pin, RCK
#define    DATA_PIN    4    // ATMEGA:  6   74HC595 SPI Data Pin, SER

#define    B_F1_PIN   5     // ATMEGA: 11   F1 Button
#define    B_F2_PIN   6     // ATMEGA: 12   F2 Button
#define    B_F3_PIN   7     // ATMEGA: 13   F3 Button
#define    B_F4_PIN   8     // ATMEGA: 14   F4 Button

#define    LED_PIN    13    // ATMEGA: 19   LED Pin, LEDPIN

#define    MIC_PIN    A0    // ATMEGA: 23   Microphone Input Pin, MIN
const uint8_t micPin = MIC_PIN;

#ifdef TEMPERATURE_ENABLE
  #define    STEM_PIN   A1  // ATMEGA: 24   Temperature Sensor Input Pin, STEM
#endif

#define    B_GROUND   9     // Bluetooth Ground Pin
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RTC_DS1307 rtc;
uint8_t global_s, global_m, global_h;
#ifdef TEMPERATURE_ENABLE
  OneWire ds(STEM_PIN);
#endif
SoftwareSerial BTSerial(B_TXD, B_RXD);

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  #endif
  pinMode(MIC_PIN, INPUT);
  #ifdef TEMPERATURE_ENABLE
    pinMode(STEM_PIN, INPUT);
  #endif

  // LED initializer
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
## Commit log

2018-01-11 Update LICENSE
2018-01-11 Firmware Source File updated to v2.1f
2018-01-11 Rename OpenVFD_2018_01_11.ino to fluorescence_2v1f.ino
2018-01-11 Rename fluorescence_2v1f.ino to openvfd_firmware.ino
2018-01-11 Updated Firmware
2018-01-11 Firmware Update 2v1f
2018-03-03 Firmware Update: Bluetooth Serial
2018-03-20 Firmware Update
    Added Night Shift setting, significant performance improvements
2018-03-20 Firmware Update (2.2rf)
    Added night shift; significant performance improvements
2018-03-21 myOpenVFD Source Code
2018-03-21 Solution File Added
2018-04-13 Rename myOpenVFD.sln to myOpenVFD/myOpenVFD.sln
2018-04-13 Rename myOpenVFD/myOpenVFD.vbproj.user to myOpenVFD/myOpenVFD/myOpenVFD.vbproj.user
2018-04-13 Revert "Rename myOpenVFD.sln to myOpenVFD/myOpenVFD.sln"
    This reverts commit 23cecd2fa212a4093a68deb3da516fc4be295a7d.
2018-04-13 Revert "Rename myOpenVFD/myOpenVFD.vbproj.user to myOpenVFD/myOpenVFD/myOpenVFD.vbproj.user"
    This reverts commit 7585cc44a90aff0fe27d23937494d23e4a1566aa.
2018-04-13 Restructure
2018-04-13 added myOpenVFD MS visual studio project
2018-04-13 OpenVFD eagle files, library added
2018-04-16 v2.21 release: bug fix
2018-04-17 Serial Documentation Added (PDF)
2018-04-22 OpenVFD Rev 3 Development Files
2018-04-25 FreeS .brd updated
2018-04-28 FreeS Update
2018-05-09 Board update
2018-07-24 FW Version 3 Development
2018-08-12 V3 development, STM32F0
2019-01-05 FW Update
2019-01-05 Firmware Version 2.3f release!
2019-01-08 Dev progress
2019-01-09 dev: xfd
2019-01-13 mode manager
2019-01-13 Arduino test drive
2019-01-14 C optimize & translate
2019-01-14 C base test run
2019-01-14 performance optimizations
2019-02-01 SCOP optimization
2019-11-17 Just some backup
2019-11-19 SK6812 STM32F0XX Driver added, in dev state
2019-11-23 fw dev
2019-11-23 Fader now polymorphic
2019-11-26 CManager Layouting
2019-11-30 Chaser Update
2019-12-20 State Backup
2019-12-21 Yess it works on hardware. Some work still needs to be done tho
2019-12-22 Fix The Bug Fug The Bix
2019-12-22 A little sensation
2019-12-23 Repeat Forever added
2020-01-02 Works, refinement badly needed
2020-01-02 This is much better
2020-01-02 HID Layout
2020-01-03 HID Works, kinda
2020-01-03 Commons: Platform independent libraries
2020-01-04 Bringing it to the clock
2020-01-04 Clock works
2020-01-05 Display UpdateÄ
2020-01-06 GUI roughly ported
2020-01-07 Removed _routines.c dependency of GUI
2020-01-08 12h & 12h NO-L0 restored
2020-01-08 a little refactor
2020-01-09 Legacy Color Modes: Spectrum, Cross & Chase Fade added, now using color_lib.c. Todo: independency of lights.c from display.h
2020-01-11 Legacy Police Light mode added (now complete); code snippets for faster class member generation
2020-01-30 Cortex M0 Code Size optimizations, performance optimizations, MomentsOfBliss first draft
2020-01-31 LerpHSL added, code size optimizations, MomentsOfBliss color optimiziations, Xorshift randomizer
2020-02-02 fixed some pretty awkward bugs. color discontinuity problems solved, Fader memory optimizations
2020-02-02 Various compile options added to lower memory usage. Objects now static inside Light_Pattern classes
2020-02-03 removed dynamic memory alloc dependency from all parts except routine & 1x GUI instance. todo: static memory pool for routine
2020-02-03 now completely free of dynamic memory allocations!
2020-02-10 VSCode Adaption, some preprocessor abuse
2020-02-12 color_chaser optimized out. Readability hopefully improved by better documentation
2020-02-13 All polymorphic dependencies removed based on assumption that only one method can be active at one time
2020-02-13 GUI and Light Patterns now have saved settings. The settings can be serialized, in simulation
2020-02-14 Serialization Backup
2020-02-15 Serialization for EEPROM done. Light Pattern Serial0/1 added. Preparing for Serial COM/BT implementation
2020-02-16 SPI now using DMA, display and lights dimmable. Next: An magnificent night shift like never before
2020-02-16 SPI now using DMA, display and lights dimmable. Next: A magnificent night shift like never before
2020-02-17 Settings can now be globally managed in config.h. One file for all settings.
2020-02-21 USB Virtual COM Port for Fluorescence is working. Sorta. Yaay.
2020-03-06 Serial Protocol compatible with myOpenVFD. Todo: New protocol, update myOpenVFD
2020-03-10 Dev of Arduino FL2.0 version
2020-03-10 FL 3.0 Firmware ported to Arduino. Should not work at this point
2020-03-15 Fluorescence App draft (formerly myOpenVFD) in Qt, platform independent
2020-03-18 FL App
2020-03-23 Fluorescence Simulator
2020-03-25 Bug fix: Clear definitions of rgb_arr length, LED protocol length and LED instance length
2020-03-26 Light Pattern Music
2020-03-27 randomizer -> utils in config.h
2020-03-28 mv commons-h -> commons/commons-h
2020-03-28 Docu Update
2020-03-31 vfdco_hid of STM now software based, much more reliable
2020-04-02 Unified default configuration, moved settings list back to config.h which makes more sense
2020-04-02 Bug fixed that would cause hsl2rgb to perform in undefined behavior on HW2 platform
2020-04-02 Better names
2020-04-12 A lot of changes. Moved fw_dev to FL3
2020-04-12 Serial Communication from and to FL2 and FLClassic works
2020-04-13 Fixed a bug that cause the dimmer of FL2 not to work
2020-04-13 Documentation
2020-04-13 Readme update
2020-04-19 DFU Mode for STM32 FL
2020-04-19 FW Updater update
2020-04-22 FL Dainty First run -> works!
2020-04-22 ReadMe for FluorescenceV3 folder
2020-04-25 Better documentation. yay.
2020-05-04 lights: f3var implemented in single color to reverse rainbow
2020-05-08 USB Type C PD breakout board, Eagle files updated
2020-05-11 USB Type C CC voltage monitoring, LTO optimized code is buggy, TODO welcome msg for Arduino
2020-05-16 Merged FLClassic & FLDainty into FL3 (HW independent), STM32F042 -> STM32L421 for more power
2020-05-17 Readability
2020-06-11 ADC fixed
2020-06-11 FL2 and FLSim Updated, util.h/c more serious now, Readme Update
2020-09-10 Library Update
2020-09-18 Bluetooth functionality for FluorescenceApp and FL2 hardware clock
2020-09-18 Bluetooth for FluorescenceApp: Responses from Fluorescence now work correctly
2020-09-21 Bluetooth Communication is working with FL3 (STM32L4)
2020-09-21 Eagle Library Update
2020-09-24 Bluetooth connection progress is now updated in app
2020-09-24 Fluorescence Simulator updated to latest code changes
2020-09-29 FluorescenceApp: Removed all dependencies of Color Widget
2020-09-29 C++ compatible struct initializers in FluorescenceApp
2020-09-29 FluorescenceApp reconfig
2020-10-03 Moments of Bliss looks just much better now
2020-10-10 FluorescenceApp now supports flashing FL2 clocks via avrdude on Mac. It's still fragile and breakable. Compiled files added (draft)
2020-10-11 FluorescenceApp Firmware update is also implemented for FL3 (STM32) now
2020-10-11 Added macOS executable for FluorescenceApp
2020-10-13 FluorescenceApp communicates with firmware version 2 without issues now. Also, updating from V2 has been tested and is working
2020-10-13 Build version of FluorescenceApp macOS updated
2020-10-14 Critical BT communication issues fixed; Load and save colors in FluorescenceApp
2020-10-14 infobox added in FluorescenceApp
2020-10-15 FL3: Fixed an issue that would cause a hardware reset to get stuck in DFU
2020-10-22 FluorescenceApp got a long overdue makeover
2020-10-22 logs removed
2020-10-23 FluorescenceApp: Fixed a bug that causes a incoming serial data to be read incorrectly
2020-10-23 FluorescenceApp: Hopefully fixed scaling on Windows; added setting time for a different time zone or universe
2020-10-23 FluorescenceApp: Layout fixes
2020-10-23 FluorescenceApp: Updating FL2 from Windows now works properly. Todo: FL3 with dfu util on Windows still bricks device; Bluetooth still doesn't work
2020-10-23 Demo Pic update
2020-10-25 FL3: NSH Improved
2020-10-25 FL2: Firmware updated
2020-10-25 FluorescenceApp: Windows 10 64 Bit pre release. dfu util recompiled to work with FL3
2020-10-29 FluorescenceApp: Qt 5.15.1 release re-build
2020-10-30 FluorescenceApp: Second half of makeover done. Made iOS/iPhone/iPad ready. It's now portrait mode and scrollable
2020-10-30 FluorescenceApp: Makeover done
2020-10-30 FluorescenceApp: macOS release, config for iOS added
2020-10-30 FluorescenceApp: Critical release patch for macOS deployed, from now on it's a zip file
2020-10-30 FluorescenceApp: Windows 64 Bit release
2020-10-31 FLSim: Updated, build folder removed
2020-12-22 Code Backup
2020-12-22 STM32L412KB -> STM32L412K8 formally migrated. Ready for release
2025-05-01 * Updated to STM32CubeMX 6.5 and migrated project to STM32CubeIDE * New feature: FINALLY!! Cross-fade and blend-fade between digits * New feature: WOHOO!! New light pattern: Pulsed cross fade * Bug f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
2025-05-21 FluorescenceApp was updated to be more robust in FW updating and to support the latest color and digit fading
2025-10-21 Sensor addition for Fluorescence

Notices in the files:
openvfd_firmware_development/cpp_base/cpp_base.ino:
MIT License
Copyright (c) 2019 Frank F. Zheng, Date: 01/05/2019
parts and their libraries:
MAX9812: License : GNU General Public License version 2 (see bottom)
Wurth_Elektronik_Passive_rev15b: Copyright: Würth Elektronik
